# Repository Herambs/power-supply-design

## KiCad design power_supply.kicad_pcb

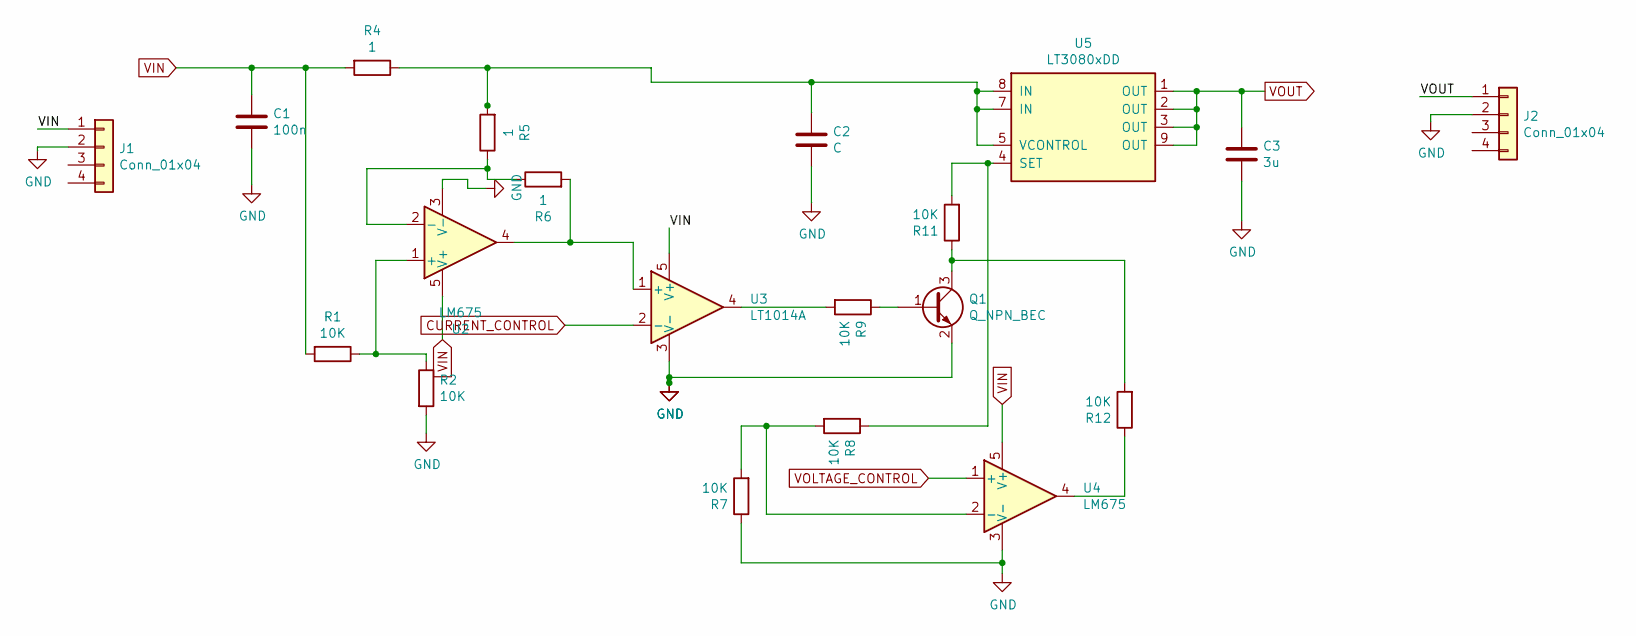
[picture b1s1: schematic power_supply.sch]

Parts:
C1: 100n; C_Rect_L4.6mm_W3.0mm_P2.50mm_MKS02_FKP02
C2: C; C_Rect_L4.6mm_W3.0mm_P2.50mm_MKS02_FKP02
C3: 3u; C_Rect_L4.6mm_W3.0mm_P2.50mm_MKS02_FKP02
J1, J2: Conn_01x04; PinHeader_1x04_P2.00mm_Vertical
Q1: Q_NPN_BEC; Crystal_HC49-U-3Pin_Vertical
R1, R2, R7, R8, R9, R11, R12: 10K; R_0603_1608Metric
R4, R5, R6: 1; R_0603_1608Metric
U2, U4: LM675; TO-220-5_P3.4x3.7mm_StaggerOdd_Lead3.8mm_Vertical
U3: LT1014A; TO-220-5_P3.4x3.7mm_StaggerOdd_Lead3.8mm_Vertical
U5: LT3080xDD; DFN-8-1EP_3x3mm_P0.5mm_EP1.66x2.38mm

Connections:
CURRENT_CONTROL: U3.2 (-)
GND: C1.2, C2.2, C3.2, J1.2, J2.2, Q1.2 (E), R2.2, R7.1, U2.3 (V-), U3.3 (V-), U4.3 (V-)
unnamed: C2.1, R4.1, R5.2, U5.5 (VCONTROL), U5.7 (IN), U5.8 (IN)
unnamed: Q1.1 (B), R9.1
unnamed: Q1.3 (C), R11.1, R12.2
unnamed: R1.1, R2.1, U2.1 (+)
unnamed: R5.1, R6.1, U2.2 (-)
unnamed: R6.2, U2.4, U3.1 (+)
unnamed: R7.2, R8.2, U4.2 (-)
unnamed: R9.2, U3.4
unnamed: R8.1, R11.2, U5.4 (SET)
unnamed: R12.1, U4.4
VIN: C1.1, J1.1, R1.2, R4.2, U2.5 (V+), U3.5 (V+), U4.5 (V+)
VOLTAGE_CONTROL: U4.1 (+)
VOUT: C3.1, J2.1, U5.1 (OUT), U5.2 (OUT), U5.3 (OUT), U5.9 (OUT)

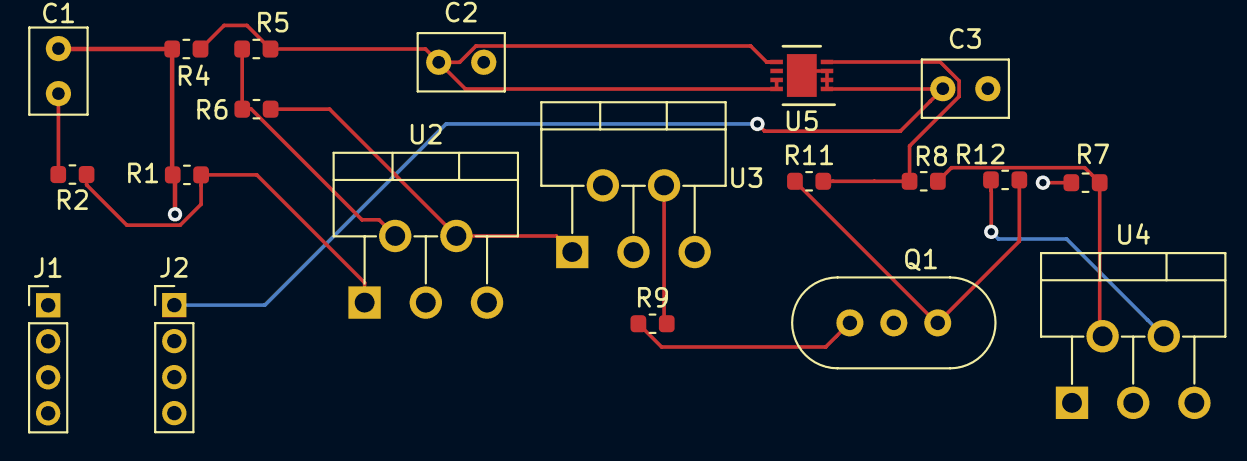
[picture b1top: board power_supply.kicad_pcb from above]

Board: 4 copper layers, 20 parts (0 on the bottom side), 13 nets.

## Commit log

2020-05-04 power_supply
